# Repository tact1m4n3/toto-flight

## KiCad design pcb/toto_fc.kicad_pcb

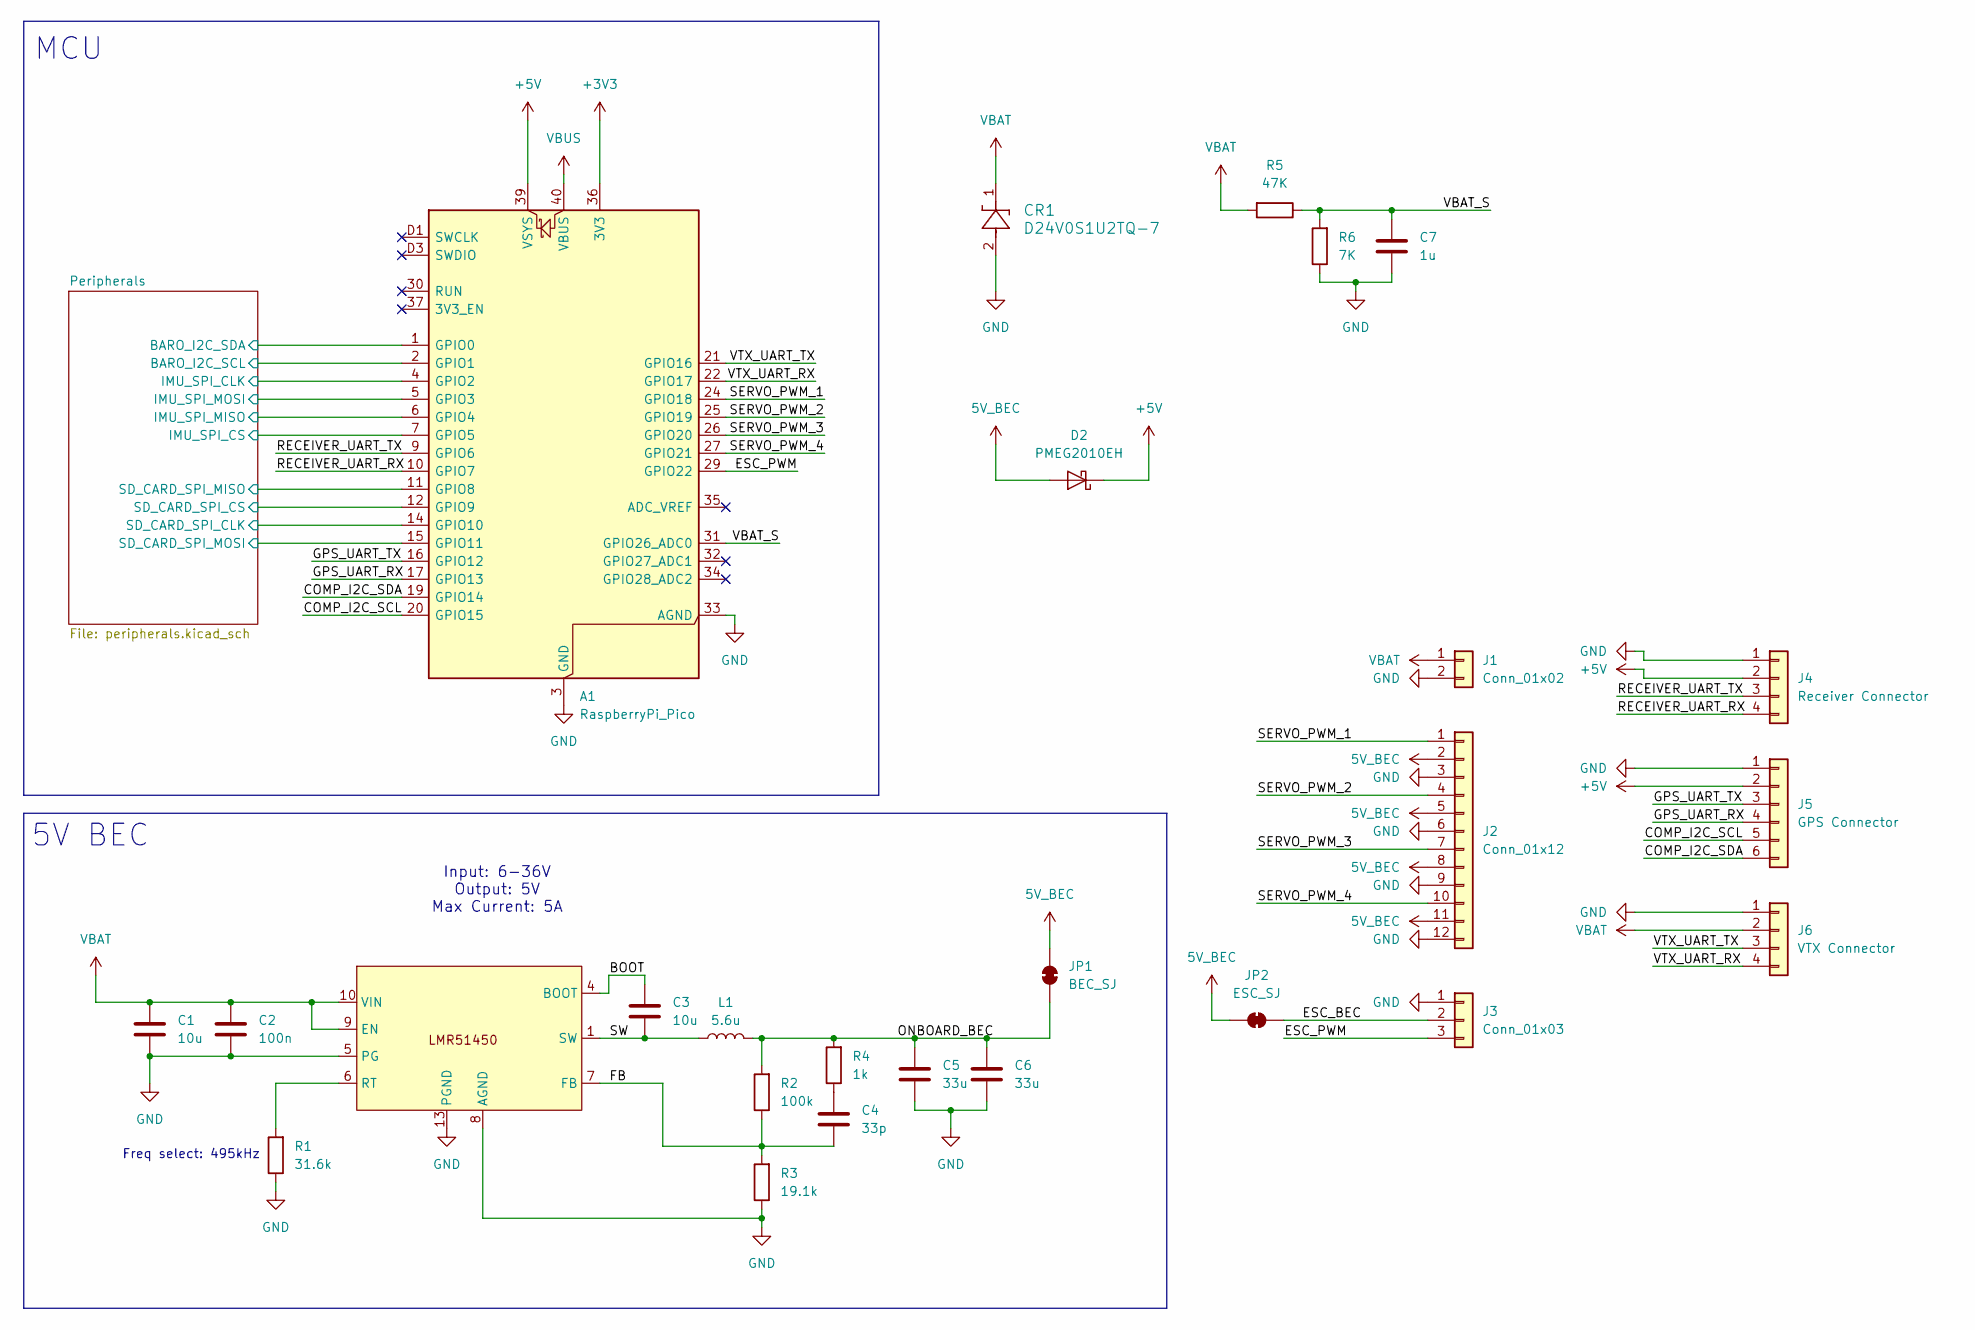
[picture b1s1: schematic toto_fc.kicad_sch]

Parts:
A1: RaspberryPi_Pico; RaspberryPi_Pico_SMD_HandSolder
C1, C3: 10u; C_0805_2012Metric
C2: 100n; C_0603_1608Metric
C4: 33p; C_0603_1608Metric
C5, C6: 33u; C_0805_2012Metric
C7: 1u; C_0603_1608Metric
CR1: D24V0S1U2TQ-7; SOD523
D2: PMEG2010EH; D_SOD-123F
J1: Conn_01x02; vbat_pads
J2: Conn_01x12; pwm_headers
J3: Conn_01x03; PinHeader_1x03_P2.54mm_Vertical
J4: Receiver Connector; 4_pads
J5: GPS Connector; 6_pads
J6: VTX Connector; 4_pads
JP1: BEC_SJ; SolderJumper-2_P1.3mm_Open_Pad1.0x1.5mm
JP2: ESC_SJ; SolderJumper-2_P1.3mm_Open_Pad1.0x1.5mm
L1: 5.6u; F1C2-060606W-5R6M
R1: 31.6k; R_0603_1608Metric
R2: 100k; R_0603_1608Metric
R3: 19.1k; R_0603_1608Metric
R4: 1k; R_0603_1608Metric
R5: 47K; R_0603_1608Metric
R6: 7K; R_0603_1608Metric
U1: LMR51450

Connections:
5V_BEC: D2.2 (A), J2.2, J2.5, J2.8, J2.11, JP1.2 (B), JP2.2 (B)
+3V3: A1.36 (3V3); also elsewhere on the board
+5V: A1.39 (VSYS), D2.1 (K), J4.2, J5.2; also elsewhere on the board
/BOOT: C3.1, U1.4 (BOOT)
/COMP_I2C_SCL: A1.20 (GPIO15), J5.5
/COMP_I2C_SDA: A1.19 (GPIO14), J5.6
/ESC_BEC: J3.2, JP2.1 (A)
/ESC_PWM: A1.29 (GPIO22), J3.3
/FB: C4.2, R2.1, R3.2, U1.7 (FB)
/GPS_UART_RX: A1.17 (GPIO13), J5.4
/GPS_UART_TX: A1.16 (GPIO12), J5.3
/ONBOARD_BEC: C5.1, C6.1, JP1.1 (A), L1.2, R2.2, R4.2
/Peripherals/BARO_I2C_SCL: A1.2 (GPIO1); also elsewhere on the board
/Peripherals/BARO_I2C_SDA: A1.1 (GPIO0); also elsewhere on the board
/Peripherals/IMU_SPI_CLK: A1.4 (GPIO2); also elsewhere on the board
/Peripherals/IMU_SPI_CS: A1.7 (GPIO5); also elsewhere on the board
/Peripherals/IMU_SPI_MISO: A1.6 (GPIO4); also elsewhere on the board
/Peripherals/IMU_SPI_MOSI: A1.5 (GPIO3); also elsewhere on the board
/Peripherals/SD_CARD_SPI_CLK: A1.14 (GPIO10); also elsewhere on the board
/Peripherals/SD_CARD_SPI_CS: A1.12 (GPIO9); also elsewhere on the board
/Peripherals/SD_CARD_SPI_MISO: A1.11 (GPIO8); also elsewhere on the board
/Peripherals/SD_CARD_SPI_MOSI: A1.15 (GPIO11); also elsewhere on the board
/RECEIVER_UART_RX: A1.10 (GPIO7), J4.4
/RECEIVER_UART_TX: A1.9 (GPIO6), J4.3
/SERVO_PWM_1: A1.24 (GPIO18), J2.1
/SERVO_PWM_2: A1.25 (GPIO19), J2.4
/SERVO_PWM_3: A1.26 (GPIO20), J2.7
/SERVO_PWM_4: A1.27 (GPIO21), J2.10
/SW: C3.2, L1.1, U1.1 (SW), U1.2 (SW), U1.3 (SW)
/VBAT_S: A1.31 (GPIO26_ADC0), C7.1, R5.1, R6.2
/VTX_UART_RX: A1.22 (GPIO17), J6.4
/VTX_UART_TX: A1.21 (GPIO16), J6.3
GND: A1.3 (GND), A1.8 (GND), A1.13 (GND), A1.18 (GND), A1.23 (GND), A1.28 (GND), A1.33 (AGND), A1.38 (GND), A1.D2 (GND), C1.2, C2.2, C5.2, C6.2, C7.2, CR1.2, J1.2, J2.3, J2.6, J2.9, J2.12, J3.1, J4.1, J5.1, J6.1, R1.1, R3.1, R6.1, U1.5 (PG), U1.8 (AGND), U1.13 (PGND); also elsewhere on the board
unnamed: C4.1, R4.1
unnamed: R1.2, U1.6 (RT)
VBAT: C1.1, C2.1, CR1.1, J1.1, J6.2, R5.2, U1.9 (EN), U1.10 (VIN), U1.11 (VIN), U1.12 (VIN)
VBUS: A1.40 (VBUS)

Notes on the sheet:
5V BEC
Freq select: 495kHz
Input: 6-36V Output: 5V Max Current: 5A
MCU

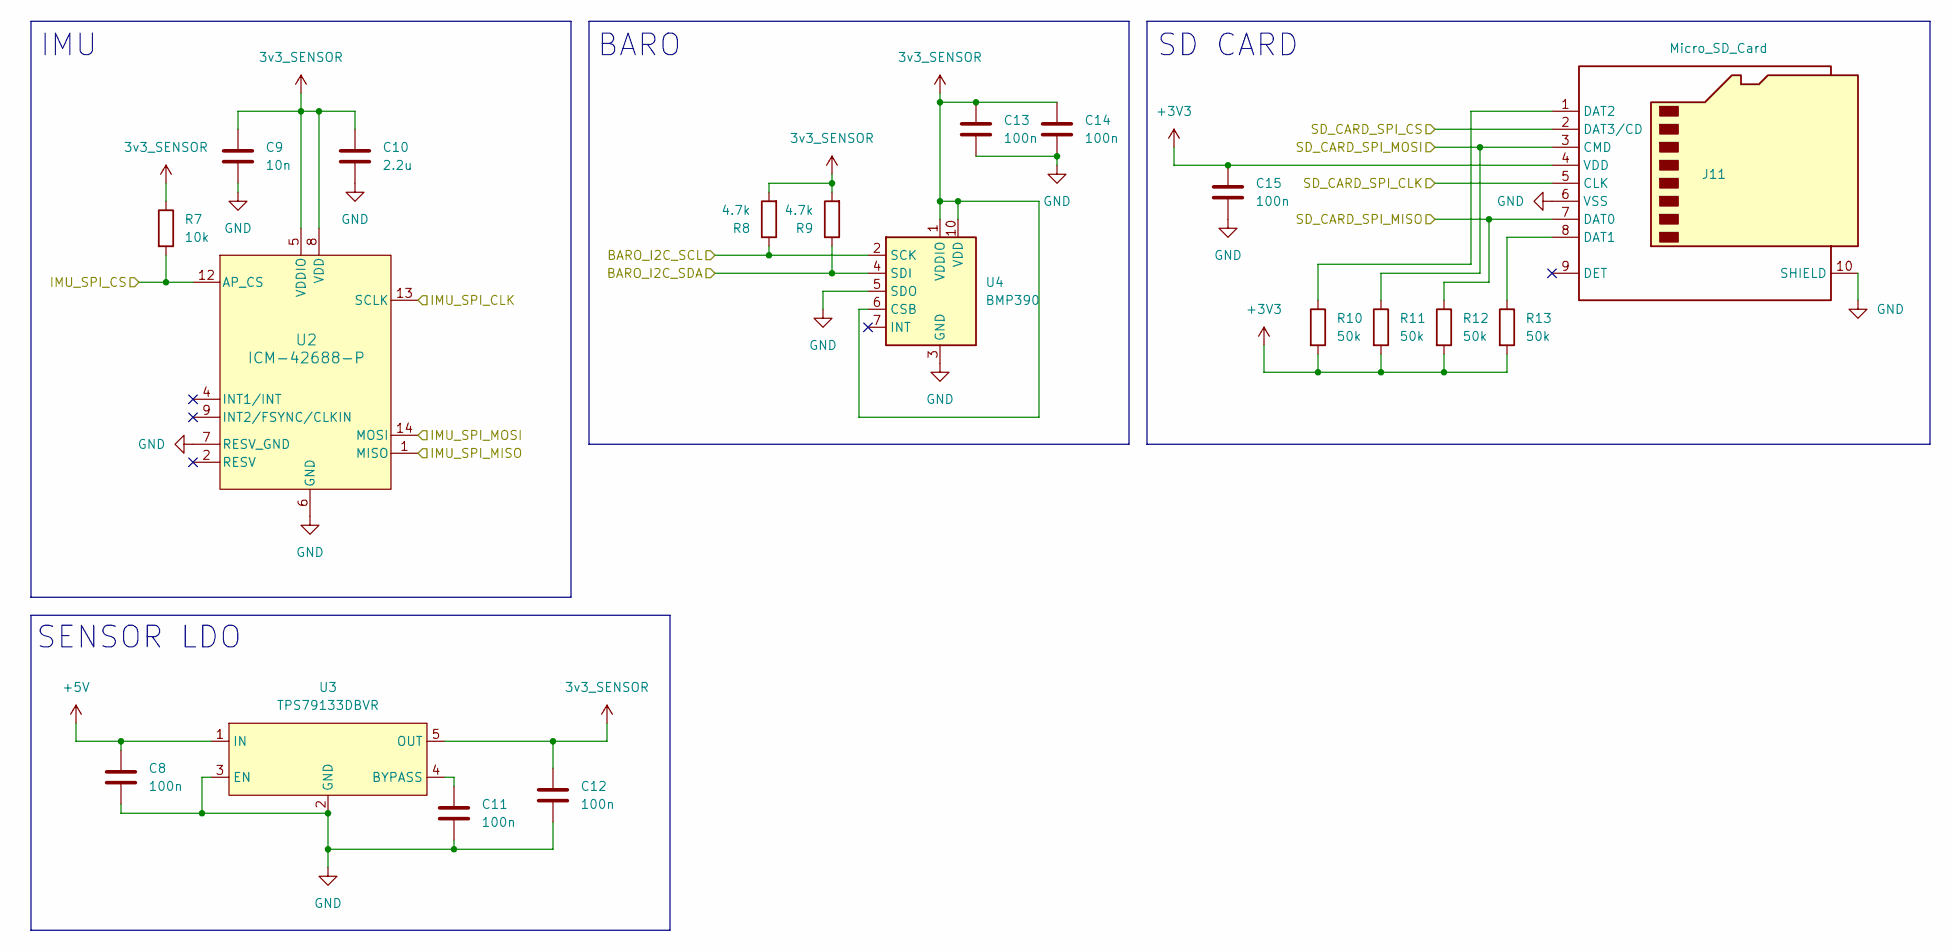
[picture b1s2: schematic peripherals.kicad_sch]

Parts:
C8, C11, C12, C13, C14, C15: 100n; C_0603_1608Metric
C9: 10n; C_0603_1608Metric
C10: 2.2u; C_0603_1608Metric
J11: Micro_SD_Card; MOLEX_104031-0811
R7: 10k; R_0603_1608Metric
R8, R9: 4.7k; R_0603_1608Metric
R10, R11, R12, R13: 50k; R_0603_1608Metric
U2: ICM-42688-P
U3: TPS79133DBVR
U4: BMP390

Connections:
3v3_SENSOR: C9.1, C10.2, C12.1, C13.1, C14.1, R7.1, R8.2, R9.2, U2.5 (VDDIO), U2.8 (VDD), U3.5 (OUT), U4.1 (VDDIO), U4.6 (CSB), U4.10 (VDD)
+3V3: C15.1, J11.4 (VDD), R10.2, R11.2, R12.2, R13.2; also elsewhere on the board
+5V: C8.1, U3.1 (IN); also elsewhere on the board
/Peripherals/BARO_I2C_SCL: R8.1, U4.2 (SCK); also elsewhere on the board
/Peripherals/BARO_I2C_SDA: R9.1, U4.4 (SDI); also elsewhere on the board
/Peripherals/IMU_SPI_CLK: U2.13 (SCLK); also elsewhere on the board
/Peripherals/IMU_SPI_CS: R7.2, U2.12 (AP_CS); also elsewhere on the board
/Peripherals/IMU_SPI_MISO: U2.1 (MISO); also elsewhere on the board
/Peripherals/IMU_SPI_MOSI: U2.14 (MOSI); also elsewhere on the board
/Peripherals/SD_CARD_SPI_CLK: J11.5 (CLK); also elsewhere on the board
/Peripherals/SD_CARD_SPI_CS: J11.2 (DAT3/CD); also elsewhere on the board
/Peripherals/SD_CARD_SPI_MISO: J11.7 (DAT0), R12.1; also elsewhere on the board
/Peripherals/SD_CARD_SPI_MOSI: J11.3 (CMD), R11.1; also elsewhere on the board
GND: C8.2, C9.2, C10.1, C11.2, C12.2, C13.2, C14.2, C15.2, J11.6 (VSS), J11.10 (SHIELD), J11.G1 (SHIELD), J11.G2 (SHIELD), J11.G3 (SHIELD), J11.G4 (SHIELD), U2.6 (GND), U2.7 (RESV_GND), U2.11 (RESV_GND), U3.2 (GND), U3.3 (EN), U4.3 (GND), U4.5 (SDO), U4.8 (GND), U4.9 (GND); also elsewhere on the board
unnamed: J11.8 (DAT1), R13.1
unnamed: J11.1 (DAT2), R10.1
unnamed: C11.1, U3.4 (BYPASS)

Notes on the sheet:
IMU
SENSOR LDO
BARO
SD CARD

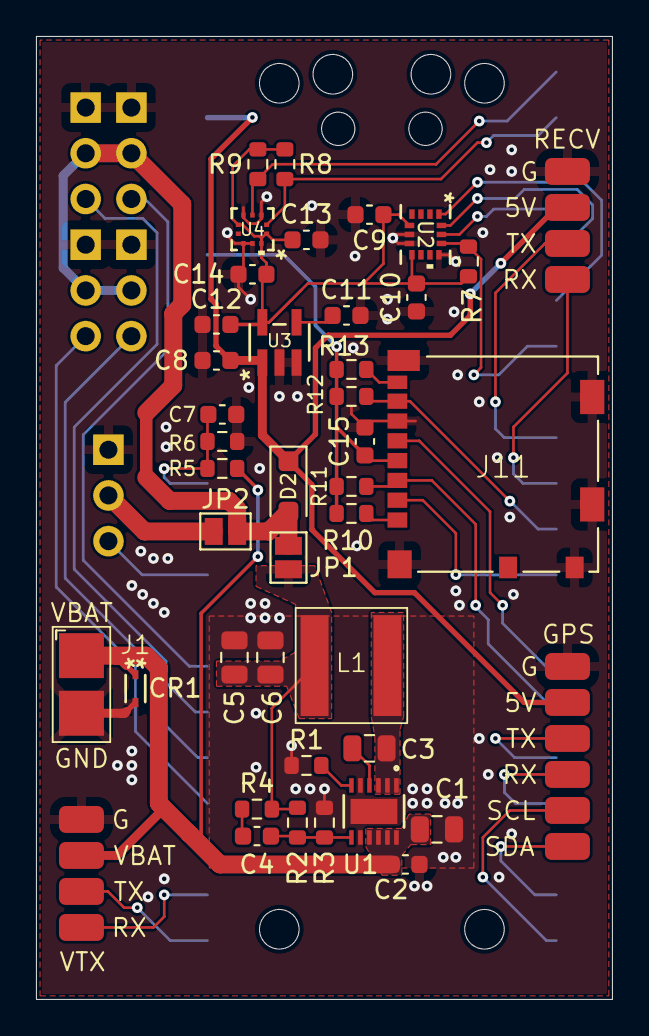
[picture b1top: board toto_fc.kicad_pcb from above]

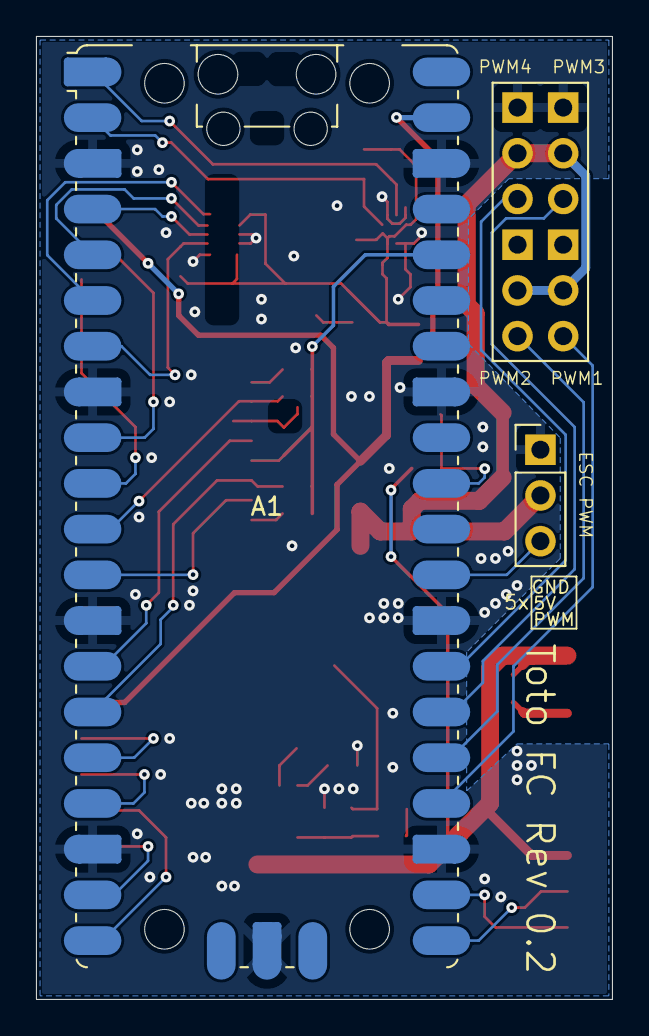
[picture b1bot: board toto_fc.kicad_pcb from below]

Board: 2 copper layers, 32.0 x 53.5 mm, 45 parts (3 on the bottom side), 40 nets.

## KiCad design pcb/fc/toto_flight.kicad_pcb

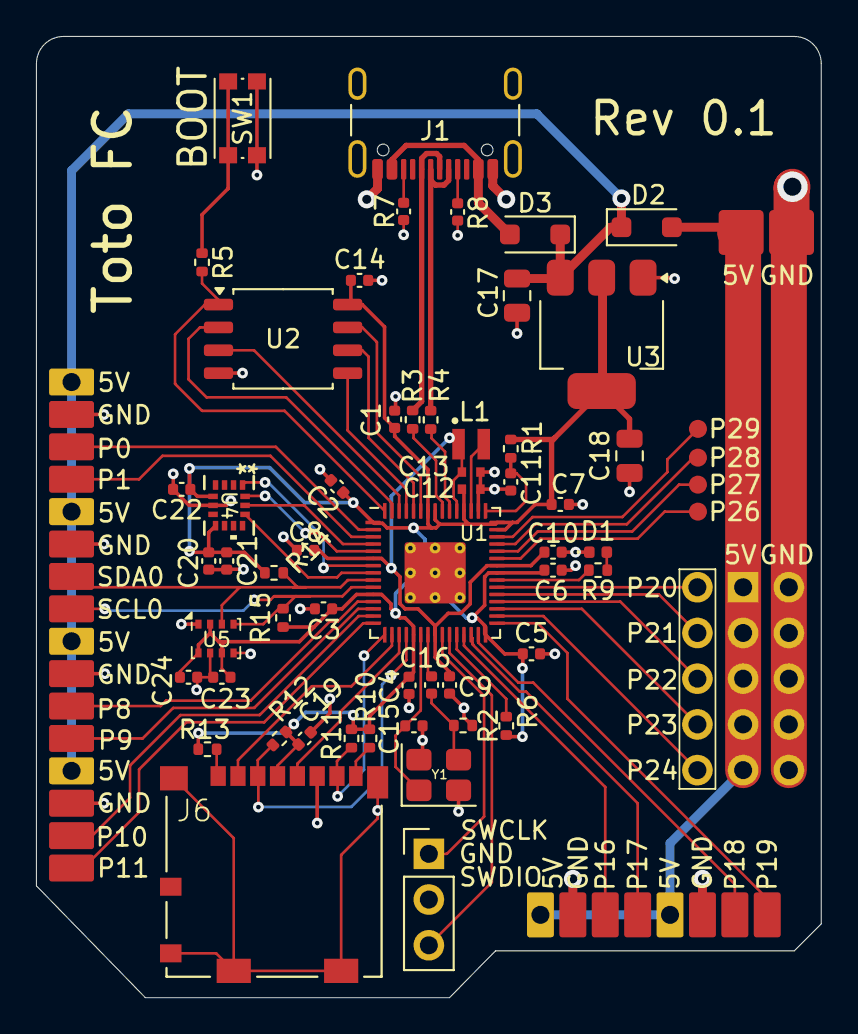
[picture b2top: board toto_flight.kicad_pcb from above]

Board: 2 copper layers, 43.6 x 53.4 mm, 58 parts (0 on the bottom side), 60 nets.

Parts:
C1, C2, C3, C4, C5, C6, C7, C8, C10, C14, C19, C20, C23, C24: 100n; C_0402_1005Metric
C9, C11: 4.7u; C_0402_1005Metric
C12, C13: 4.7u; C_0402_1005Metric_small_pads
C15, C16: 15p; C_0402_1005Metric
C17, C18: 10u; C_0805_2012Metric
C21: 2.2u; C_0402_1005Metric
C22: 10n; C_0402_1005Metric
D1: LED; LED_0402_1005Metric
D2, D3: PMEG2020EH; D_SOD-123F
J1: USB_C; USB_C_017
J2: Conn_01x03; PinHeader_1x03_P2.54mm_Vertical
J3: Conn_01x16; gpio_pads
J4: Conn_01x15; pwm_pins
J5: Conn_01x02; esc_power_pads
J6: Micro_SD_Card; MOLEX_104031-0811
J7: Conn_01x08; gpio_2_pads
J8: Conn_01x04; analog_pads
L1: 3.3u; L_pol_2016
R1: 33; R_0402_1005Metric
R2: 1k; R_0402_1005Metric
R3, R4: 27; R_0402_1005Metric
R5: 1K; R_0402_1005Metric
R6: 10k; R_0402_1005Metric
R7, R8: 5.1k; C_0402_1005Metric
R9: 470; R_0402_1005Metric
R10, R11, R12, R13: 50k; R_0402_1005Metric
R14, R15: 2.2k; R_0402_1005Metric
SW1: SW_Push; SW_Push_1P1T_NO_CK_KMR2
U1: RP2350_60QFN; RP2350-QFN-60-1EP_7x7_P0.4mm_EP3.4x3.4mm_ThermalVias
U2: W25Q128JVS; SOIC-8_5.3x5.3mm_P1.27mm
U3: NCP1117-3.3_SOT223; SOT-223-3_TabPin2
U4: ICM-42688-P; LGA14_2P5X3X0P91_TDK
U5: BMP280
Y1: ABM8-272-T3; Crystal_SMD_3225-4Pin_3.2x2.5mm

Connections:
5V_BEC_IN: D2.2 (A), J4.2, J4.5, J4.8, J4.11, J4.14, J5.1, J7.1, J7.5
+1V1: C8.1, C9.1, C10.1, C13.1, L1.1, U1.6 (DVDD), U1.23 (DVDD), U1.39 (DVDD), U1.50 (VREG_FB)
+3V3: C1.1, C2.1, C3.1, C4.1, C5.1, C6.1, C7.1, C12.1, C14.1, C18.1, C19.1, C20.1, C21.1, C22.1, C23.1, C24.2, J6.4 (VDD), R1.2, R6.1, R10.2, R11.2, R12.2, R13.2, R14.2, R15.2, U1.1 (IOVDD), U1.11 (IOVDD), U1.20 (IOVDD), U1.30 (IOVDD), U1.38 (IOVDD), U1.44 (ADC_AVDD), U1.45 (IOVDD), U1.49 (VREG_VIN), U1.53 (USB_OTP_VDD), U1.54 (QSPI_IOVDD), U2.8 (VCC), U3.2 (VO), U4.5 (VDDIO), U4.8 (VDD), U5.2 (CSB), U5.6 (VDDIO), U5.8 (VDD)
+5V: C17.1, D2.1 (K), D3.1 (K), J3.1, J3.5, J3.9, J3.13, U3.3 (VI)
GND: C1.2, C2.2, C3.2, C4.2, C5.2, C6.2, C7.2, C8.2, C9.2, C10.2, C11.2, C12.2, C13.2, C14.2, C15.1, C17.2, C18.2, C19.2, C20.2, C21.2, C22.2, C23.2, C24.1, D1.1 (K), J1.A1B12 (GND), J1.B1A12 (GND), J2.2, J3.2, J3.6, J3.10, J3.14, J4.3, J4.6, J4.9, J4.12, J4.15, J5.2, J6.6 (VSS), J6.10 (SHIELD), J6.G1 (SHIELD), J6.G2 (SHIELD), J6.G3 (SHIELD), J6.G4 (SHIELD), J7.2, J7.6, R2.2, R7.2, R8.2, SW1.1, U1.47 (VREG_PGND), U1.61 (GND), U2.4 (GND), U3.1 (GND), U4.6 (GND), U5.1 (GND), U5.5 (SDO), U5.7 (GND), Y1.2, Y1.4
GP0: J3.3, U1.2 (GPIO0)
GP1: J3.4, U1.3 (GPIO1)
GP8: J3.11, U1.12 (GPIO8)
GP9: J3.12, U1.13 (GPIO9)
GP10: J3.15, U1.14 (GPIO10)
GP11: J3.16, U1.15 (GPIO11)
GP16: J7.3, U1.27 (GPIO16)
GP17: J7.4, U1.28 (GPIO17)
GP18: J7.7, U1.29 (GPIO18)
GP19: J7.8, U1.31 (GPIO19)
GP20: J4.1, U1.32 (GPIO20)
GP21: J4.4, U1.33 (GPIO21)
GP22: J4.7, U1.34 (GPIO22)
GP23: J4.10, U1.35 (GPIO23)
GP24: J4.13, U1.36 (GPIO24)
GP26: J8.1, U1.40 (GPIO26_ADC0)
GP27: J8.2, U1.41 (GPIO27_ADC1)
GP28: J8.3, U1.42 (GPIO28_ADC2)
GP29: J8.4, U1.43 (GPIO29_ADC3)
I2C0_SCL: J3.8, R15.1, U1.10 (GPIO7), U5.4 (SCK)
I2C0_SDA: J3.7, R14.1, U1.9 (GPIO6), U5.3 (SDI)
LED: R9.1, U1.37 (GPIO25)
unnamed: C16.2, R2.1, Y1.3
unnamed: D1.2 (A), R9.2
unnamed: J1.A5 (CC1), R8.1
unnamed: J1.B5 (CC2), R7.1
unnamed: J6.8 (DAT1), R10.1
unnamed: J6.1 (DAT2), R13.1
unnamed: R5.1, SW1.2
unnamed: R4.1, U1.51 (USB_DM)
unnamed: R3.1, U1.52 (USB_DP)
unnamed: C11.1, R1.1, U1.46 (VREG_AVDD)
unnamed: L1.2, U1.48 (VREG_LX)
QSPI_CLK: U1.56 (QSPI_SCLK), U2.6 (CLK)
QSPI_SD0: U1.57 (QSPI_SD0), U2.5 (DI/IO_{0})
QSPI_SD1: U1.59 (QSPI_SD1), U2.2 (DO/IO_{1})
QSPI_SD2: U1.58 (QSPI_SD2), U2.3 (~WP/IO_{2})
QSPI_SD3: U1.55 (QSPI_SD3), U2.7 (~HOLD/~RESET/IO_{3})
QSPI_SS: R5.2, U1.60 (QSPI_SS), U2.1 (~CS)
RUN: R6.2, U1.26 (RUN)
SPI0_CLK: U1.4 (GPIO2), U4.13 (AP_SCL/AP_SCLK)
SPI0_CS_IMU: U1.8 (GPIO5), U4.12 (AP_CS)
SPI0_RX: U1.7 (GPIO4), U4.1 (AP_SDO/AP_AD0)
SPI0_TX: U1.5 (GPIO3), U4.14 (AP_SDA/AP_SDIO/AP_SDI)
SPI1_CLK: J6.5 (CLK), U1.18 (GPIO14)
SPI1_CS_SD_CARD: J6.2 (DAT3/CD), U1.17 (GPIO13)
SPI1_RX: J6.7 (DAT0), R11.1, U1.16 (GPIO12)
SPI1_TX: J6.3 (CMD), R12.1, U1.19 (GPIO15)
SWCLK: J2.1, U1.24 (SWCLK)
SWD: J2.3, U1.25 (SWD)
USB_D+: J1.A6 (D+), J1.B6 (D+), R3.2
USB_D-: J1.A7 (D-), J1.B7 (D-), R4.2
VBUS: D3.2 (A), J1.A4B9 (VBUS), J1.B4A9 (VBUS)
XIN: C15.2, U1.21 (XIN), Y1.1
XOUT: C16.1, U1.22 (XOUT)

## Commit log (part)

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2025-09-09 Add README.md
2025-09-09 Add MIT License
2025-09-12 reorganize
2025-10-01 progress
2025-10-02 rename pcbs
2025-10-08 fc_board: More schematic progress
2025-10-13 Huge huge refactor and use pico
2025-10-20 More pcb work
2025-10-21 More work on the pcb
2025-10-24 more progress
2025-10-25 More work
2025-10-27 Finished PCB
2025-10-28 Add gitignore
2025-11-12 Fix firmware building
